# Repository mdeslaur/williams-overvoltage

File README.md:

# Williams Overvoltage board

This is a reproduction Williams Overvoltage board as used on the Stargate
power supply, and can be used on the Defender power supply as well.

Williams part number #5773-09664-00.

Details about this board can be found here:

https://archive.org/details/arcademanual_stargate-ds/page/n11

This isn't an exact copy, the pcb routing and size is different as I didn't
possess an original board for comparison.

Marc Deslauriers
2019-07-11

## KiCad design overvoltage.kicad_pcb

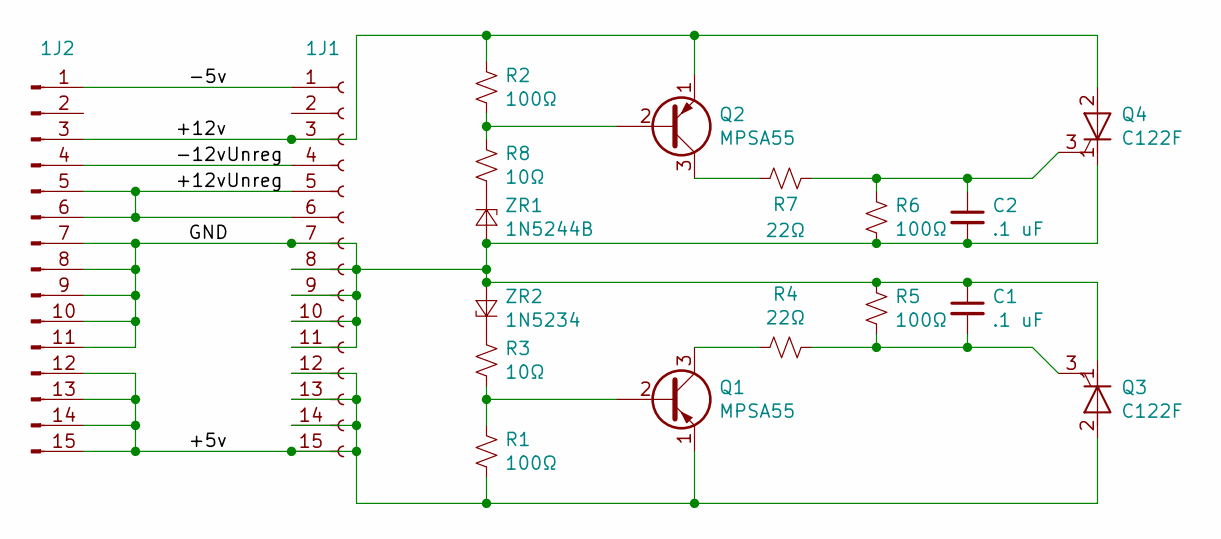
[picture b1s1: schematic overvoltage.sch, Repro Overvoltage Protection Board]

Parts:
1J1: Conn_01x15_Female; TE_1-640384-5
1J2: Conn_01x15_Male; TE_1-640384-5
C1, C2: .1 uF; C_Axial_L5.1mm_D3.1mm_P10.00mm_Horizontal
Q1, Q2: MPSA55; TO-92
Q3, Q4: C122F; TO-220-3_Horizontal_TabDown
R1, R2, R5, R6: 100Ω; R_Axial_DIN0207_L6.3mm_D2.5mm_P10.16mm_Horizontal
R3, R8: 10Ω; R_Axial_DIN0207_L6.3mm_D2.5mm_P10.16mm_Horizontal
R4, R7: 22Ω; R_Axial_DIN0207_L6.3mm_D2.5mm_P10.16mm_Horizontal
ZR1: 1N5244B; D_A-405_P10.16mm_Horizontal
ZR2: 1N5234; D_A-405_P10.16mm_Horizontal

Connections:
/+5v: 1J1.12, 1J1.13, 1J1.14, 1J1.15, 1J2.12, 1J2.13, 1J2.14, 1J2.15, Q1.1 (E), Q3.2 (A), R1.2
/+12v: 1J1.3, 1J2.3, Q2.1 (E), Q4.2 (A), R2.1
/+12vUnreg: 1J1.5, 1J1.6, 1J2.5, 1J2.6
/-5v: 1J1.1, 1J2.1
/-12vUnreg: 1J1.4, 1J2.4
/GND: 1J1.7, 1J1.8, 1J1.9, 1J1.10, 1J1.11, 1J2.7, 1J2.8, 1J2.9, 1J2.10, 1J2.11, C1.1, C2.2, Q3.1 (K), Q4.1 (K), R5.1, R6.2, ZR1.2 (A), ZR2.2 (A)
unnamed: C1.2, Q3.3 (G), R4.1, R5.2
unnamed: C2.1, Q4.3 (G), R6.1, R7.1
unnamed: Q1.2 (B), R1.1, R3.2
unnamed: Q1.3 (C), R4.2
unnamed: Q2.2 (B), R2.2, R8.1
unnamed: Q2.3 (C), R7.2
unnamed: R3.1, ZR2.1 (K)
unnamed: R8.2, ZR1.1 (K)

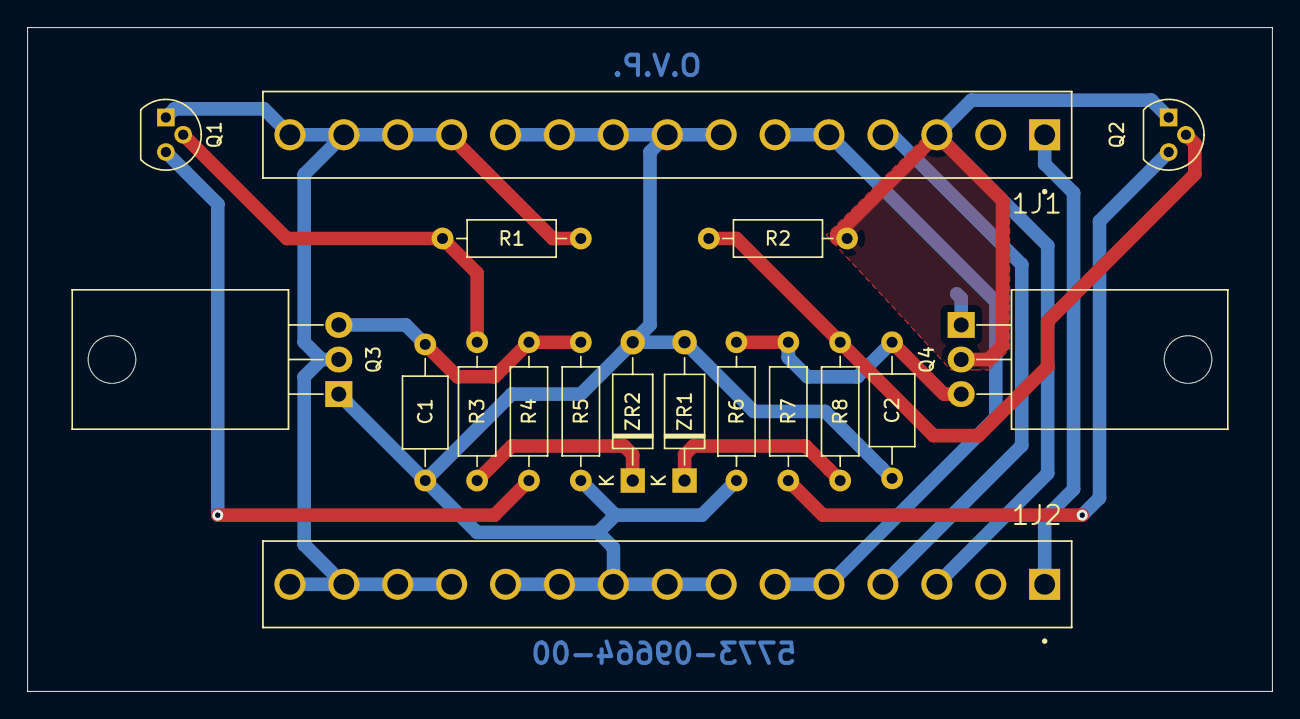
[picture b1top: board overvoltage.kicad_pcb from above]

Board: 2 copper layers, 91.4 x 48.8 mm, 18 parts (0 on the bottom side), 14 nets.

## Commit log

2019-07-11 added .gitignore file
2019-07-11 added README.md
2019-07-13 add part number
2022-10-25 added schematic to pdf directory
